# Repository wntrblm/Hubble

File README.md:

# Hubble

Hubble is Winterbloom's re-usable development board for test jigs.

## Repository layout

This repository contains the hardware design files and firmware files for Hubble.

- **firmware/** contains the firmware source code, build scripts, and third-party dependencies. The firmware is written in C using GCC ARM.
- **hardware/** contains the hardware design files for the mainboard, jackboard, panel, and programming board. These are all created using KiCAD.
- **mechanical/** contains various designs for laser-cut and 3d-printed parts used to modify the stock test jig assembly for Hubble.

## License and contributing

Hubble is open-source hardware and software, however, licensing a project like this is a little complicated. Please take a chance to review the [LICENSE](LICENSE.md) file.

We welcome contributions! Please read our [Contributing Guide](CONTRIBUTING.md) and [Code of Conduct](CODE_OF_CONDUCT.md).

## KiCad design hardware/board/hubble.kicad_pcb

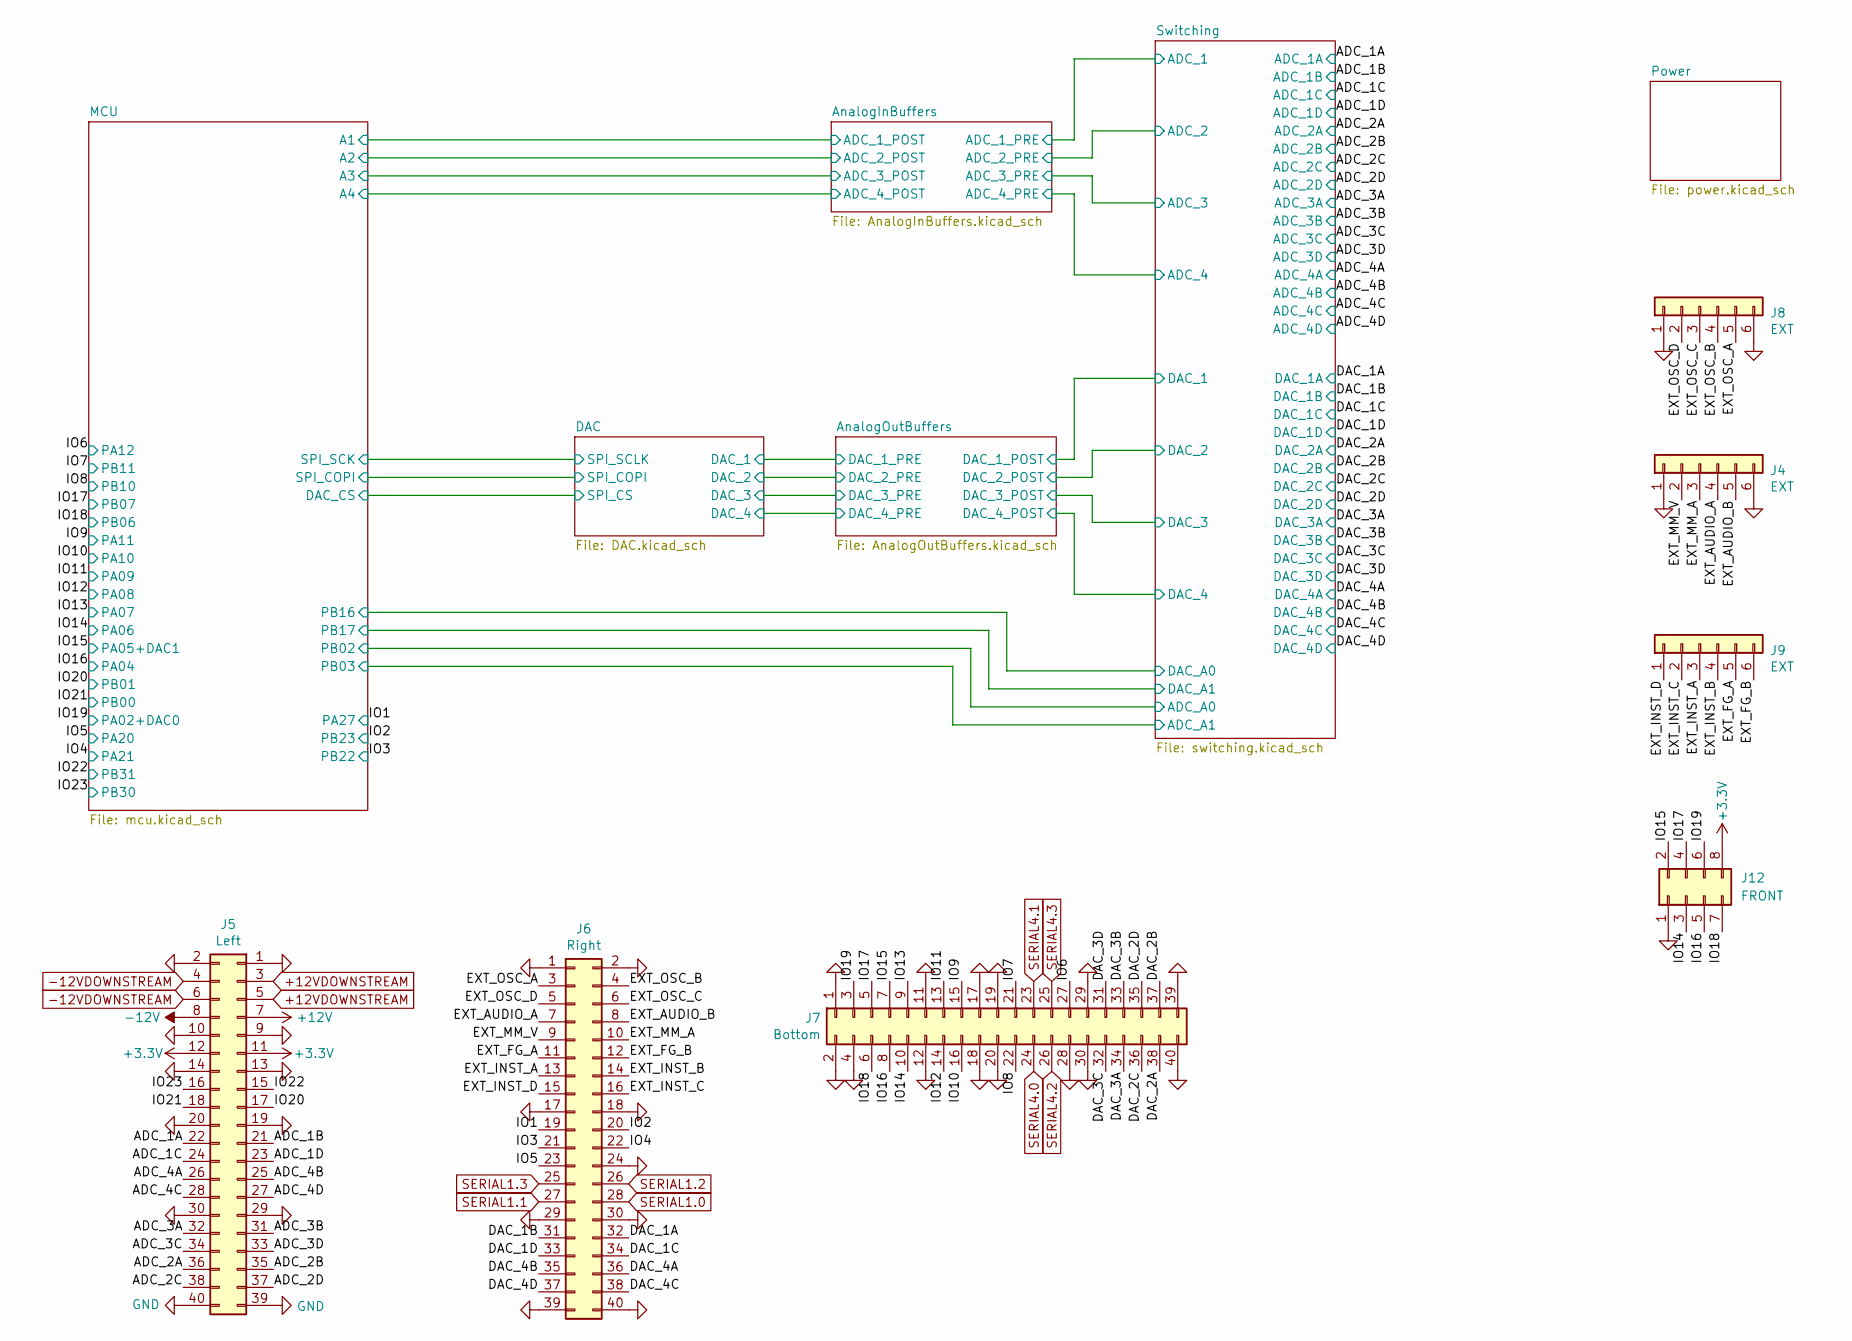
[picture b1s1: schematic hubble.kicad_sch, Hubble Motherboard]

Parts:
J4, J8, J9: EXT; SolderWire-0.75sqmm_1x06_P4.8mm_D1.25mm_OD2.3mm
J5: Left; PinSocket_2x20_P2.54mm_Vertical
J6: Right; PinSocket_2x20_P2.54mm_Vertical
J7: Bottom; PinSocket_2x20_P2.54mm_Vertical
J12: FRONT; PinHeader_2x04_P2.54mm_Vertical

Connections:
+12V: J5.7; also elsewhere on the board
+12VDOWNSTREAM: J5.3, J5.5; also elsewhere on the board
-12V: J5.8; also elsewhere on the board
-12VDOWNSTREAM: J5.4, J5.6; also elsewhere on the board
/ADC_1A: J5.22; also elsewhere on the board
/ADC_1B: J5.21; also elsewhere on the board
/ADC_1C: J5.24; also elsewhere on the board
/ADC_1D: J5.23; also elsewhere on the board
/ADC_2A: J5.36; also elsewhere on the board
/ADC_2B: J5.35; also elsewhere on the board
/ADC_2C: J5.38; also elsewhere on the board
/ADC_2D: J5.37; also elsewhere on the board
/ADC_3A: J5.32; also elsewhere on the board
/ADC_3B: J5.31; also elsewhere on the board
/ADC_3C: J5.34; also elsewhere on the board
/ADC_3D: J5.33; also elsewhere on the board
/ADC_4A: J5.26; also elsewhere on the board
/ADC_4B: J5.25; also elsewhere on the board
/ADC_4C: J5.28; also elsewhere on the board
/ADC_4D: J5.27; also elsewhere on the board
/DAC_1A: J6.32; also elsewhere on the board
/DAC_1B: J6.31; also elsewhere on the board
/DAC_1C: J6.34; also elsewhere on the board
/DAC_1D: J6.33; also elsewhere on the board
/DAC_2A: J7.38; also elsewhere on the board
/DAC_2B: J7.37; also elsewhere on the board
/DAC_2C: J7.36; also elsewhere on the board
/DAC_2D: J7.35; also elsewhere on the board
/DAC_3A: J7.34; also elsewhere on the board
/DAC_3B: J7.33; also elsewhere on the board
/DAC_3C: J7.32; also elsewhere on the board
/DAC_3D: J7.31; also elsewhere on the board
/DAC_4A: J6.36; also elsewhere on the board
/DAC_4B: J6.35; also elsewhere on the board
/DAC_4C: J6.38; also elsewhere on the board
/DAC_4D: J6.37; also elsewhere on the board
/EXT_AUDIO_A: J4.4, J6.7
/EXT_AUDIO_B: J4.5, J6.8
/EXT_FG_A: J6.11, J9.5
/EXT_FG_B: J6.12, J9.6
/EXT_INST_A: J6.13, J9.3
/EXT_INST_B: J6.14, J9.4
/EXT_INST_C: J6.16, J9.2
/EXT_INST_D: J6.15, J9.1
/EXT_MM_A: J4.3, J6.10
/EXT_MM_V: J4.2, J6.9
/EXT_OSC_A: J6.3, J8.5
/EXT_OSC_B: J6.4, J8.4
/EXT_OSC_C: J6.6, J8.3
/EXT_OSC_D: J6.5, J8.2
/IO1: J6.19; also elsewhere on the board
/IO2: J6.20; also elsewhere on the board
/IO3: J6.21; also elsewhere on the board
/IO4: J6.22; also elsewhere on the board
/IO5: J6.23; also elsewhere on the board
/IO6: J7.27; also elsewhere on the board
/IO7: J7.21; also elsewhere on the board
/IO8: J7.22; also elsewhere on the board
/IO9: J7.15; also elsewhere on the board
/IO10: J7.16; also elsewhere on the board
/IO11: J7.13; also elsewhere on the board
/IO12: J7.14; also elsewhere on the board
/IO13: J7.9; also elsewhere on the board
/IO14: J7.10, J12.3; also elsewhere on the board
/IO15: J7.7, J12.2; also elsewhere on the board
/IO16: J7.8, J12.5; also elsewhere on the board
/IO17: J7.5, J12.4; also elsewhere on the board
/IO18: J7.6, J12.7; also elsewhere on the board
/IO19: J7.3, J12.6; also elsewhere on the board
/IO20: J5.17; also elsewhere on the board
/IO21: J5.18; also elsewhere on the board
/IO22: J5.15; also elsewhere on the board
/IO23: J5.16; also elsewhere on the board
GND: J4.1, J4.6, J5.1, J5.2, J5.9, J5.10, J5.13, J5.14, J5.19, J5.20, J5.29, J5.30, J5.39, J5.40, J6.1, J6.2, J6.17, J6.18, J6.24, J6.29, J6.30, J6.39, J6.40, J7.1, J7.2, J7.4, J7.11, J7.12, J7.17, J7.18, J7.19, J7.20, J7.28, J7.29, J7.30, J7.39, J7.40, J8.1, J8.6, J12.1; also elsewhere on the board
SERIAL1.0: J6.28; also elsewhere on the board
SERIAL1.1: J6.27; also elsewhere on the board
SERIAL1.2: J6.26; also elsewhere on the board
SERIAL1.3: J6.25; also elsewhere on the board
SERIAL4.0: J7.24; also elsewhere on the board
SERIAL4.1: J7.23; also elsewhere on the board
SERIAL4.2: J7.26; also elsewhere on the board
SERIAL4.3: J7.25; also elsewhere on the board

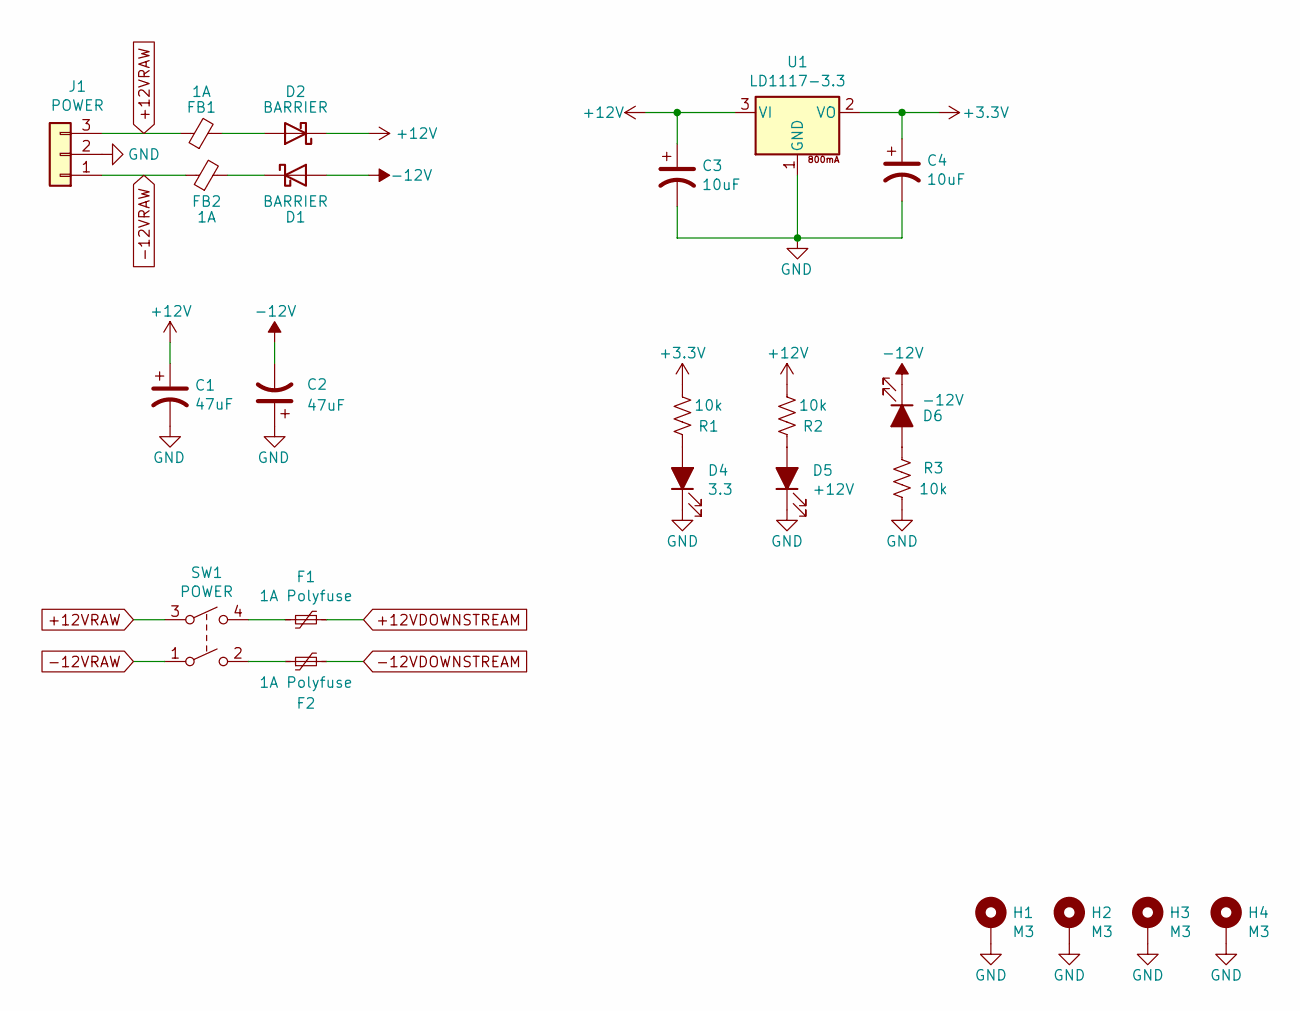
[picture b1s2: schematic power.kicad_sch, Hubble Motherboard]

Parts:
C1, C2: 47uF; CP_Radial_D5.0mm_P2.50mm
C3, C4: 10uF; CP_Radial_D5.0mm_P2.50mm
D1, D2: BARRIER; DIODE_SOD-123_SOD-123F
D4: 3.3; LED_0805_Kingbright_APT2012
D5: +12V; LED_0805_Kingbright_APT2012
D6: -12V; LED_0805_Kingbright_APT2012
F1, F2: 1A Polyfuse; Littelfuse_0805L; mpn 0805L075
FB1, FB2: 1A; L_0603_1608Metric_Pad1.05x0.95mm_HandSolder
H1, H2, H3, H4: M3; MountingHole_3.2mm_M3_Pad_Via
J1: POWER; SolderWire-0.75sqmm_1x03_P4.8mm_D1.25mm_OD2.3mm
R1, R2, R3: 10k; R_0603_1608Metric_Pad0.98x0.95mm_HandSolder
SW1: POWER; SolderWire-0.75sqmm_1x04_P4.8mm_D1.25mm_OD2.3mm
U1: LD1117-3.3; SOT-223-3_TabPin2; mpn LM1117IMP-3.3

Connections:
+12V: C1.1, C3.1, D2.1 (K), R2.1, U1.3 (VI); also elsewhere on the board
+12VDOWNSTREAM: F1.1; also elsewhere on the board
+12VRAW: FB1.1, J1.3, SW1.3
-12V: C2.2, D1.2 (A), D6.1 (K); also elsewhere on the board
-12VDOWNSTREAM: F2.2; also elsewhere on the board
-12VRAW: FB2.1, J1.1, SW1.1
GND: C1.2, C2.1, C3.2, C4.2, D4.1 (K), D5.1 (K), H1.1, H2.1, H3.1, H4.1, J1.2, R3.1, U1.1 (GND); also elsewhere on the board
unnamed: D1.1 (K), FB2.2
unnamed: D2.2 (A), FB1.2
unnamed: D4.2 (A), R1.2
unnamed: D5.2 (A), R2.2
unnamed: D6.2 (A), R3.2
unnamed: F1.2, SW1.4
unnamed: F2.1, SW1.2

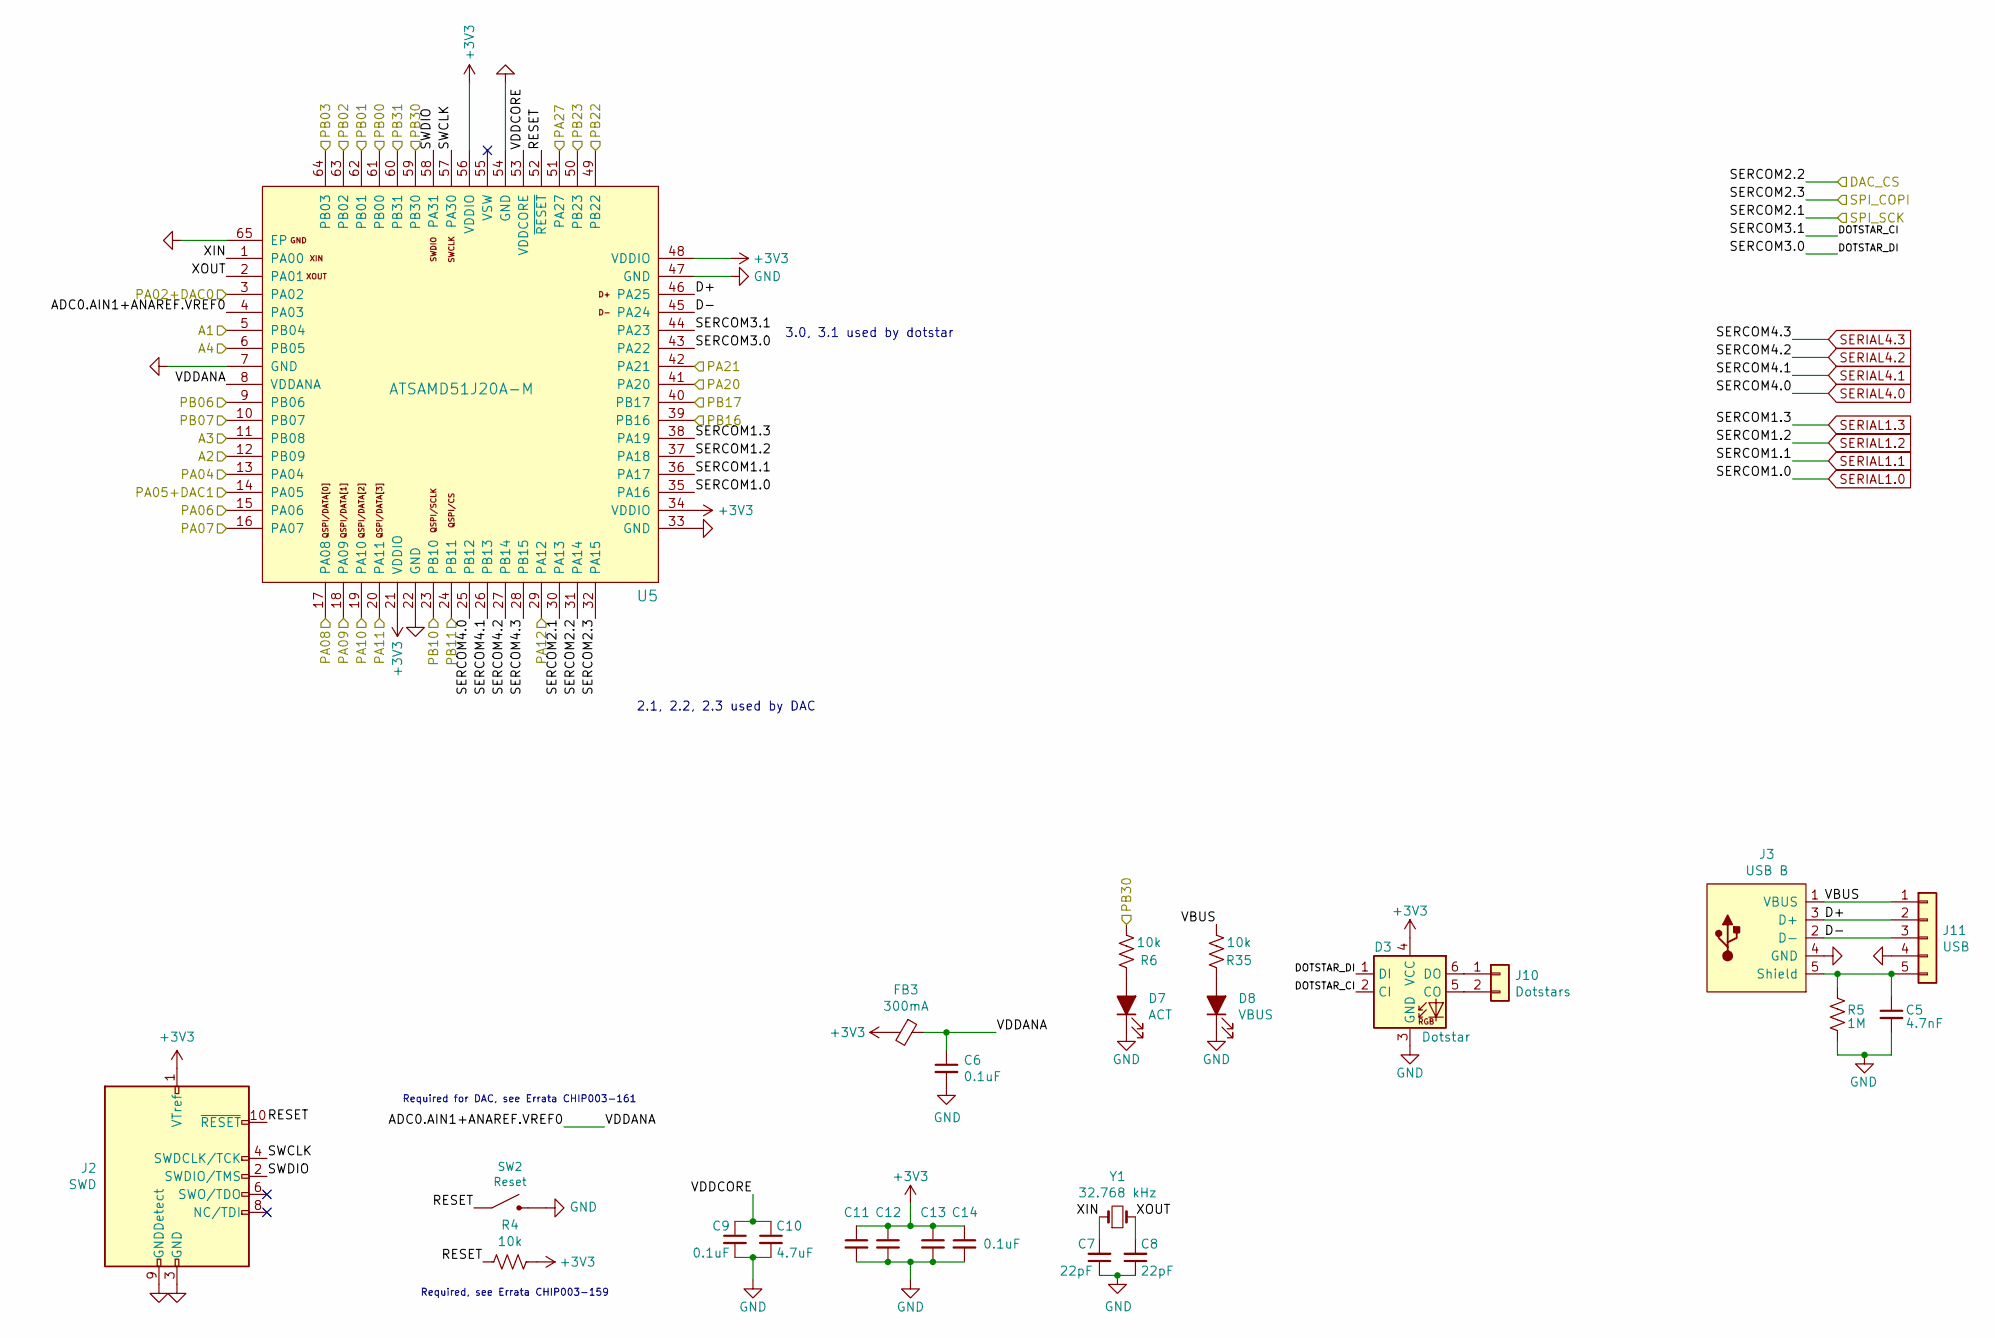
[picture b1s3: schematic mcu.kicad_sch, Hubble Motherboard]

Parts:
C5: 4.7nF; C_0603_1608Metric_Pad1.08x0.95mm_HandSolder
C6, C9, C11, C12, C13, C14: 0.1uF; C_0603_1608Metric_Pad1.08x0.95mm_HandSolder
C7, C8: 22pF; C_0603_1608Metric_Pad1.08x0.95mm_HandSolder
C10: 4.7uF; C_0603_1608Metric_Pad1.08x0.95mm_HandSolder
D3: Dotstar; Dotstar_5050; mpn SK9822
D7: ACT; LED_0805_Kingbright_APT2012
D8: VBUS; LED_0805_Kingbright_APT2012
FB3: 300mA; L_0603_1608Metric_Pad1.05x0.95mm_HandSolder
J2: SWD; PinHeader_2x05_P1.27mm_Vertical
J3: USB B; USB_B_OST_USB-B1HSxx_Horizontal; mpn 5787834-1
J10: Dotstars; PinHeader_1x02_P2.54mm_Vertical
J11: USB; PinHeader_1x05_P2.54mm_Vertical
R4, R6, R35: 10k; R_0603_1608Metric_Pad0.98x0.95mm_HandSolder
R5: 1M; R_0805_2012Metric_Pad1.20x1.40mm_HandSolder
SW2: Reset; Tactile_Switch_4.2mm; mpn MF-SW-TACT-4.2MM, MF-SW-TACT-6MM
U5: ATSAMD51J20A-M; QFN+QFP-64-SAMD51; mpn ATSAMD51J20A-M
Y1: 32.768 kHz; Crystal_SMD_2012-2Pin_2.0x1.2mm_HandSoldering

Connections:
/DAC/SPI_COPI: U5.32 (PA15); also elsewhere on the board
/IO1: U5.51 (PA27); also elsewhere on the board
/IO2: U5.50 (PB23); also elsewhere on the board
/IO3: U5.49 (PB22); also elsewhere on the board
/IO4: U5.42 (PA21); also elsewhere on the board
/IO5: U5.41 (PA20); also elsewhere on the board
/IO6: U5.29 (PA12); also elsewhere on the board
/IO7: U5.24 (PB11); also elsewhere on the board
/IO8: U5.23 (PB10); also elsewhere on the board
/IO9: U5.20 (PA11); also elsewhere on the board
/IO10: U5.19 (PA10); also elsewhere on the board
/IO11: U5.18 (PA09); also elsewhere on the board
/IO12: U5.17 (PA08); also elsewhere on the board
/IO13: U5.16 (PA07); also elsewhere on the board
/IO14: U5.15 (PA06); also elsewhere on the board
/IO15: U5.14 (PA05); also elsewhere on the board
/IO16: U5.13 (PA04); also elsewhere on the board
/IO17: U5.10 (PB07); also elsewhere on the board
/IO18: U5.9 (PB06); also elsewhere on the board
/IO19: U5.3 (PA02); also elsewhere on the board
/IO20: U5.62 (PB01); also elsewhere on the board
/IO21: U5.61 (PB00); also elsewhere on the board
/IO22: U5.60 (PB31); also elsewhere on the board
/IO23: R6.1, U5.59 (PB30); also elsewhere on the board
/MCU/ADC0.AIN1+ANAREF.VREF0: C6.1, FB3.1, U5.4 (PA03), U5.8 (VDDANA)
/MCU/D+: J3.3 (D+), J11.2, U5.46 (PA25)
/MCU/D-: J3.2 (D-), J11.3, U5.45 (PA24)
/MCU/DAC_CS: U5.31 (PA14); also elsewhere on the board
/MCU/DOTSTAR_CI: D3.2 (CI), U5.44 (PA23)
/MCU/DOTSTAR_DI: D3.1 (DI), U5.43 (PA22)
/MCU/RESET: J2.10 (~RESET), R4.1, SW2.1, U5.52 (~RESET)
/MCU/SPI_SCK: U5.30 (PA13); also elsewhere on the board
/MCU/SWCLK: J2.4 (SWDCLK/TCK), U5.57 (PA30)
/MCU/SWDIO: J2.2 (SWDIO/TMS), U5.58 (PA31)
/MCU/VBUS: J3.1 (VBUS), J11.1, R35.1
/MCU/VDDCORE: C9.1, C10.1, U5.53 (VDDCORE)
/MCU/XIN: C7.2, U5.1 (PA00), Y1.1
/MCU/XOUT: C8.2, U5.2 (PA01), Y1.2
/Switching/ADC_A0: U5.63 (PB02); also elsewhere on the board
/Switching/ADC_A1: U5.64 (PB03); also elsewhere on the board
/Switching/DAC_A0: U5.39 (PB16); also elsewhere on the board
/Switching/DAC_A1: U5.40 (PB17); also elsewhere on the board
GND: C5.2, C6.2, C7.1, C8.1, C9.2, C10.2, C11.2, C12.2, C13.2, C14.2, D3.3 (GND), D7.1 (K), D8.1 (K), J2.3 (GND), J2.5 (GND), J2.9 (GNDDetect), J3.4 (GND), J11.4, R5.2, SW2.2, U5.7 (GND), U5.22 (GND), U5.33 (GND), U5.47 (GND), U5.54 (GND), U5.65 (EP); also elsewhere on the board
unnamed: C5.1, J3.5 (Shield), J11.5, R5.1
unnamed: D3.5 (CO), J10.2
unnamed: D3.6 (DO), J10.1
unnamed: D7.2 (A), R6.2
unnamed: D8.2 (A), R35.2
SERIAL1.0: U5.35 (PA16); also elsewhere on the board
SERIAL1.1: U5.36 (PA17); also elsewhere on the board
SERIAL1.2: U5.37 (PA18); also elsewhere on the board
SERIAL1.3: U5.38 (PA19); also elsewhere on the board
SERIAL4.0: U5.25 (PB12); also elsewhere on the board
SERIAL4.1: U5.26 (PB13); also elsewhere on the board
SERIAL4.2: U5.27 (PB14); also elsewhere on the board
SERIAL4.3: U5.28 (PB15); also elsewhere on the board

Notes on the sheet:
2.1, 2.2, 2.3 used by DAC
3.0, 3.1 used by dotstar
Required, see Errata CHIP003-159
Required for DAC, see Errata CHIP003-161

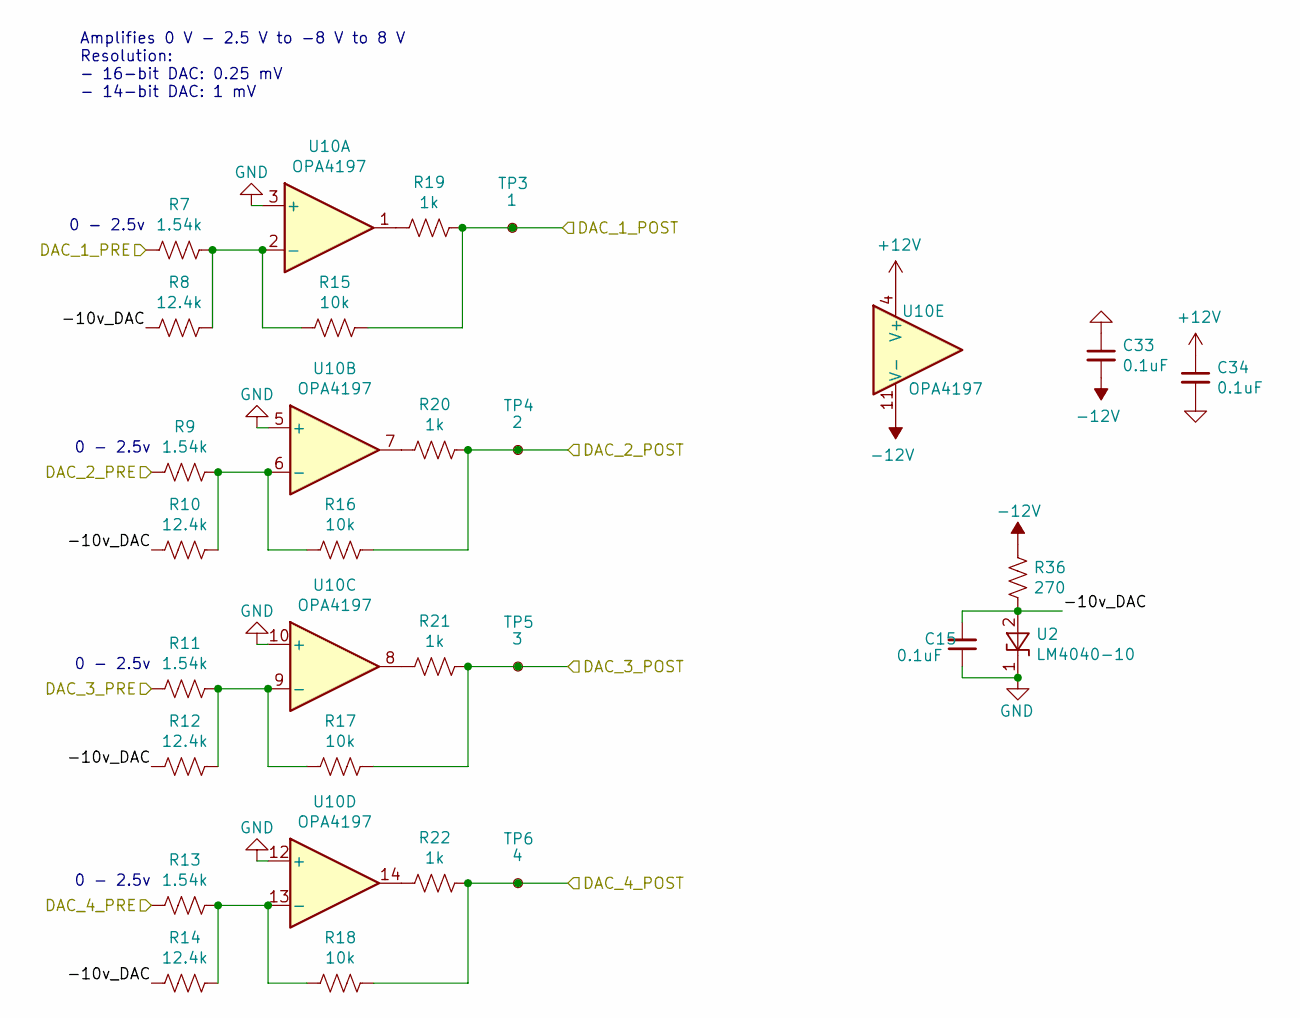
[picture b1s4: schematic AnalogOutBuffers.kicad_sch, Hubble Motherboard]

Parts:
C15, C33, C34: 0.1uF; C_0603_1608Metric_Pad1.08x0.95mm_HandSolder
R7, R9, R11, R13: 1.54k; R_0603_1608Metric_Pad0.98x0.95mm_HandSolder
R8, R10, R12, R14: 12.4k; R_0603_1608Metric_Pad0.98x0.95mm_HandSolder
R15, R16, R17, R18: 10k; R_0603_1608Metric_Pad0.98x0.95mm_HandSolder
R19, R20, R21, R22: 1k; R_0603_1608Metric_Pad0.98x0.95mm_HandSolder
R36: 270; R_0603_1608Metric_Pad0.98x0.95mm_HandSolder
TP3: 1; TestPoint_Pad_D1.0mm
TP4: 2; TestPoint_Pad_D1.0mm
TP5: 3; TestPoint_Pad_D1.0mm
TP6: 4; TestPoint_Pad_D1.0mm
U2: LM4040-10; SOT-23; mpn LM4040DIM3-10.0/NOPB
U10: OPA4197; TSSOP-14_4.4x5mm_P0.65mm; mpn OPA4197IPW

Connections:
+12V: C34.1, U10.4 (V+); also elsewhere on the board
-12V: C33.2, R36.1, U10.11 (V-); also elsewhere on the board
/AnalogOutBuffers/-10v_DAC: C15.2, R8.2, R10.2, R12.2, R14.2, R36.2, U2.2 (A)
/DAC/DAC_1: R7.2; also elsewhere on the board
/DAC/DAC_2: R9.2; also elsewhere on the board
/DAC/DAC_3: R11.2; also elsewhere on the board
/DAC/DAC_4: R13.2; also elsewhere on the board
/Switching/DAC_1: R15.1, R19.1, TP3.1; also elsewhere on the board
/Switching/DAC_2: R16.1, R20.1, TP4.1; also elsewhere on the board
/Switching/DAC_3: R17.1, R21.1, TP5.1; also elsewhere on the board
/Switching/DAC_4: R18.1, R22.1, TP6.1; also elsewhere on the board
GND: C15.1, C33.1, C34.2, U2.1 (K), U10.3 (+), U10.5 (+), U10.10 (+), U10.12 (+); also elsewhere on the board
unnamed: R9.1, R10.1, R16.2, U10.6 (-)
unnamed: R11.1, R12.1, R17.2, U10.9 (-)
unnamed: R13.1, R14.1, R18.2, U10.13 (-)
unnamed: R7.1, R8.1, R15.2, U10.2 (-)
unnamed: R19.2, U10.1
unnamed: R20.2, U10.7
unnamed: R21.2, U10.8
unnamed: R22.2, U10.14

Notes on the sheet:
0 - 2.5v
Amplifies 0 V - 2.5 V to -8 V to 8 V Resolution: - 16-bit DAC: 0.25 mV - 14-bit DAC: 1 mV

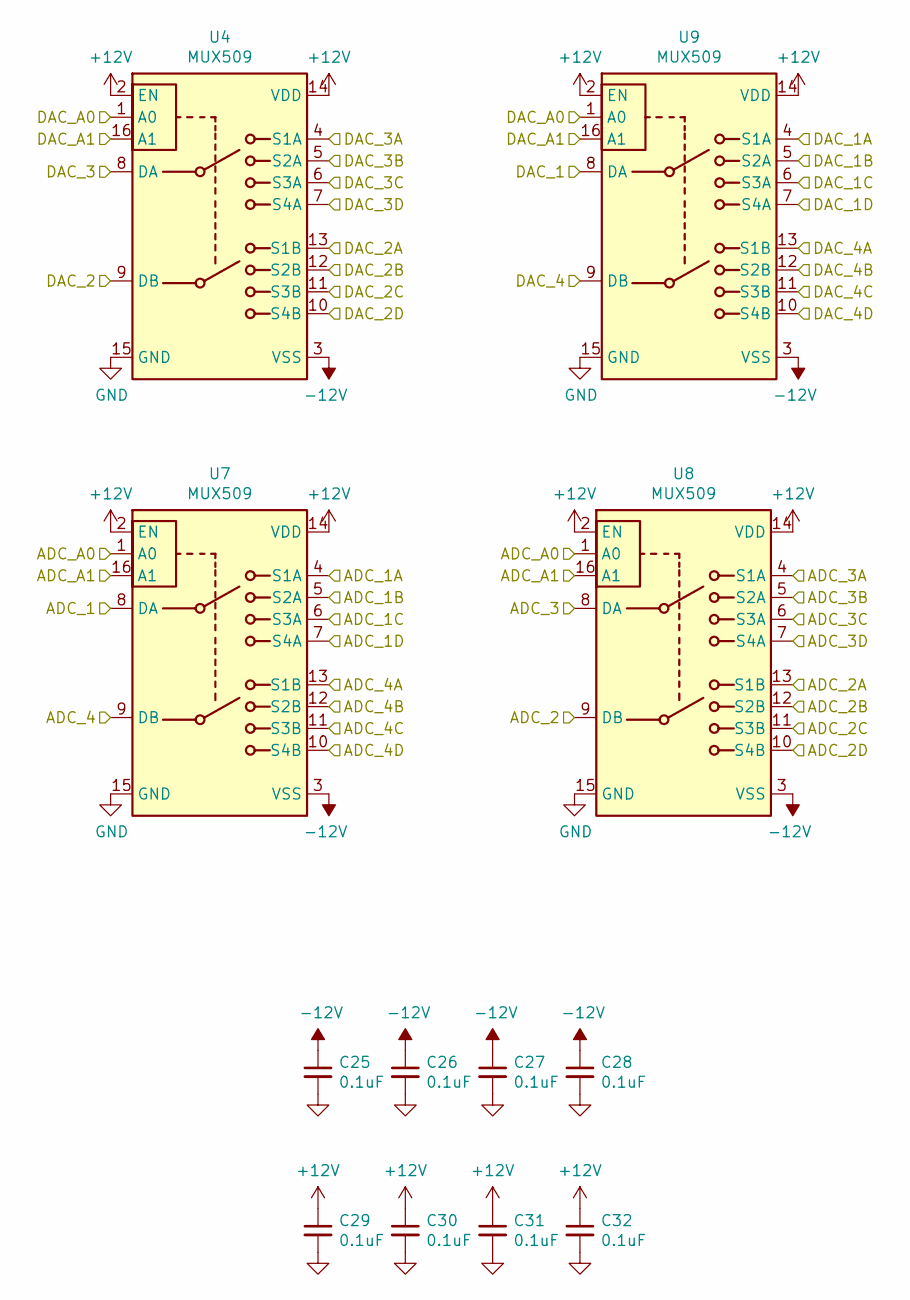
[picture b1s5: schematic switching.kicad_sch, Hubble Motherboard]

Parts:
C25, C26, C27, C28, C29, C30, C31, C32: 0.1uF; C_0603_1608Metric_Pad1.08x0.95mm_HandSolder
U4, U7, U8, U9: MUX509; TSSOP-16_4.4x5mm_P0.65mm

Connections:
+12V: C29.1, C30.1, C31.1, C32.1, U4.2 (EN), U4.14 (VDD), U7.2 (EN), U7.14 (VDD), U8.2 (EN), U8.14 (VDD), U9.2 (EN), U9.14 (VDD); also elsewhere on the board
-12V: C25.1, C26.1, C27.1, C28.1, U4.3 (VSS), U7.3 (VSS), U8.3 (VSS), U9.3 (VSS); also elsewhere on the board
/ADC_1A: U7.4 (S1A); also elsewhere on the board
/ADC_1B: U7.5 (S2A); also elsewhere on the board
/ADC_1C: U7.6 (S3A); also elsewhere on the board
/ADC_1D: U7.7 (S4A); also elsewhere on the board
/ADC_2A: U8.13 (S1B); also elsewhere on the board
/ADC_2B: U8.12 (S2B); also elsewhere on the board
/ADC_2C: U8.11 (S3B); also elsewhere on the board
/ADC_2D: U8.10 (S4B); also elsewhere on the board
/ADC_3A: U8.4 (S1A); also elsewhere on the board
/ADC_3B: U8.5 (S2A); also elsewhere on the board
/ADC_3C: U8.6 (S3A); also elsewhere on the board
/ADC_3D: U8.7 (S4A); also elsewhere on the board
/ADC_4A: U7.13 (S1B); also elsewhere on the board
/ADC_4B: U7.12 (S2B); also elsewhere on the board
/ADC_4C: U7.11 (S3B); also elsewhere on the board
/ADC_4D: U7.10 (S4B); also elsewhere on the board
/DAC_1A: U9.4 (S1A); also elsewhere on the board
/DAC_1B: U9.5 (S2A); also elsewhere on the board
/DAC_1C: U9.6 (S3A); also elsewhere on the board
/DAC_1D: U9.7 (S4A); also elsewhere on the board
/DAC_2A: U4.13 (S1B); also elsewhere on the board
/DAC_2B: U4.12 (S2B); also elsewhere on the board
/DAC_2C: U4.11 (S3B); also elsewhere on the board
/DAC_2D: U4.10 (S4B); also elsewhere on the board
/DAC_3A: U4.4 (S1A); also elsewhere on the board
/DAC_3B: U4.5 (S2A); also elsewhere on the board
/DAC_3C: U4.6 (S3A); also elsewhere on the board
/DAC_3D: U4.7 (S4A); also elsewhere on the board
/DAC_4A: U9.13 (S1B); also elsewhere on the board
/DAC_4B: U9.12 (S2B); also elsewhere on the board
/DAC_4C: U9.11 (S3B); also elsewhere on the board
/DAC_4D: U9.10 (S4B); also elsewhere on the board
/Switching/ADC_1: U7.8 (DA); also elsewhere on the board
/Switching/ADC_2: U8.9 (DB); also elsewhere on the board
/Switching/ADC_3: U8.8 (DA); also elsewhere on the board
/Switching/ADC_4: U7.9 (DB); also elsewhere on the board
/Switching/ADC_A0: U7.1 (A0), U8.1 (A0); also elsewhere on the board
/Switching/ADC_A1: U7.16 (A1), U8.16 (A1); also elsewhere on the board
/Switching/DAC_1: U9.8 (DA); also elsewhere on the board
/Switching/DAC_2: U4.9 (DB); also elsewhere on the board
/Switching/DAC_3: U4.8 (DA); also elsewhere on the board
/Switching/DAC_4: U9.9 (DB); also elsewhere on the board
/Switching/DAC_A0: U4.1 (A0), U9.1 (A0); also elsewhere on the board
/Switching/DAC_A1: U4.16 (A1), U9.16 (A1); also elsewhere on the board
GND: C25.2, C26.2, C27.2, C28.2, C29.2, C30.2, C31.2, C32.2, U4.15 (GND), U7.15 (GND), U8.15 (GND), U9.15 (GND); also elsewhere on the board

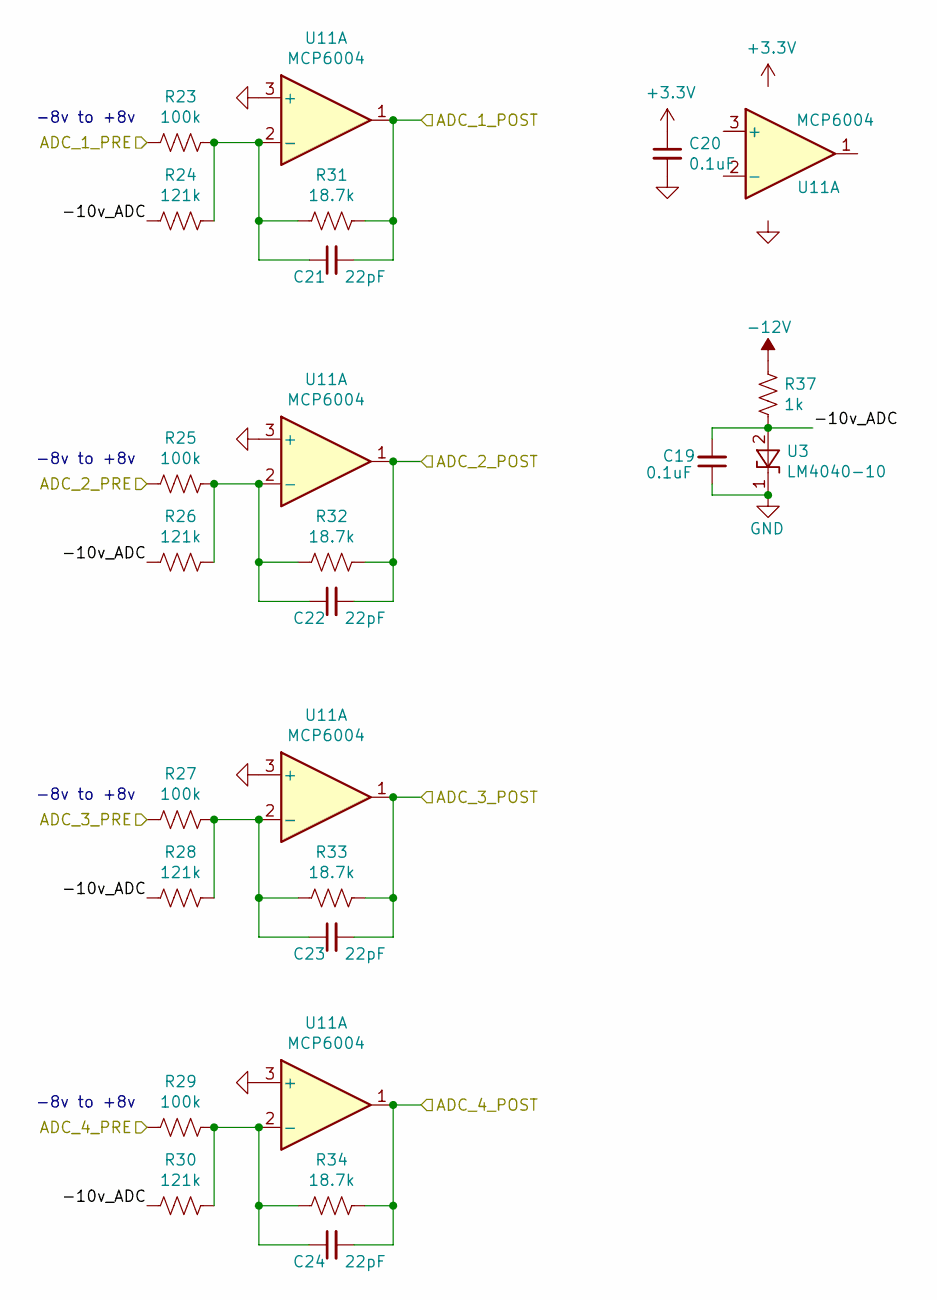
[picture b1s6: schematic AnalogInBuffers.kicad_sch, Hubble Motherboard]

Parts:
C19, C20: 0.1uF; C_0603_1608Metric_Pad1.08x0.95mm_HandSolder
C21, C22, C23, C24: 22pF; C_0603_1608Metric_Pad1.08x0.95mm_HandSolder
R23, R25, R27, R29: 100k; R_0603_1608Metric_Pad0.98x0.95mm_HandSolder
R24, R26, R28, R30: 121k; R_0603_1608Metric_Pad0.98x0.95mm_HandSolder
R31, R32, R33, R34: 18.7k; R_0603_1608Metric_Pad0.98x0.95mm_HandSolder
R37: 1k; R_0603_1608Metric_Pad0.98x0.95mm_HandSolder
U3: LM4040-10; SOT-23; mpn LM4040DIM3-10.0/NOPB
U11: MCP6004; TSSOP-14_4.4x5mm_P0.65mm; mpn MCP6004T-I/ST, MCP6004T-E/ST

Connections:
-12V: R37.1; also elsewhere on the board
/AnalogInBuffers/-10v_ADC: C19.2, R24.2, R26.2, R28.2, R30.2, R37.2, U3.2 (A)
/Switching/ADC_1: R23.2; also elsewhere on the board
/Switching/ADC_2: R25.2; also elsewhere on the board
/Switching/ADC_3: R27.2; also elsewhere on the board
/Switching/ADC_4: R29.2; also elsewhere on the board
GND: C19.1, C20.2, U3.1 (K), U11.3 (+), U11.5 (+), U11.10 (+), U11.11 (V-), U11.12 (+); also elsewhere on the board

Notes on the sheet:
-8v to +8v

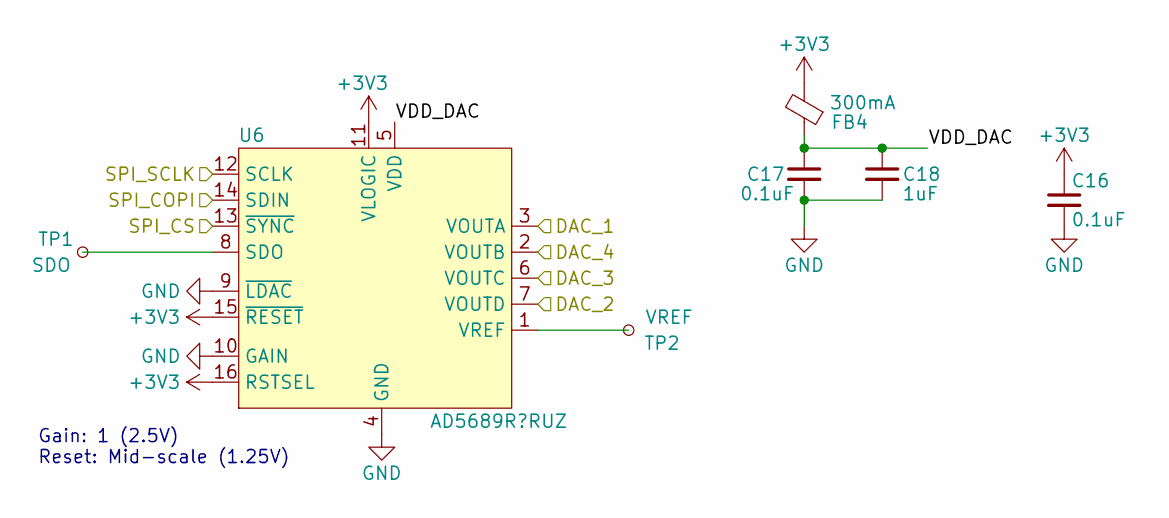
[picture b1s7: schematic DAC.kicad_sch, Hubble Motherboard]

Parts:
C16, C17: 0.1uF; C_0603_1608Metric_Pad1.08x0.95mm_HandSolder
C18: 1uF; C_0603_1608Metric_Pad1.08x0.95mm_HandSolder
FB4: 300mA; L_0603_1608Metric_Pad1.05x0.95mm_HandSolder
TP1: SDO; TestPoint_Pad_D1.0mm
TP2: VREF; TestPoint_Pad_D1.0mm
U6: AD5689R?RUZ; TSSOP-16_4.4x5mm_P0.65mm; mpn AD5685ARUZ, AD5685BRUZ

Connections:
/DAC/DAC_1: U6.3 (VOUTA); also elsewhere on the board
/DAC/DAC_2: U6.7 (VOUTD); also elsewhere on the board
/DAC/DAC_3: U6.6 (VOUTC); also elsewhere on the board
/DAC/DAC_4: U6.2 (VOUTB); also elsewhere on the board
/DAC/SPI_COPI: U6.14 (SDIN); also elsewhere on the board
/DAC/VDD_DAC: C17.1, C18.1, FB4.1, U6.5 (VDD)
/MCU/DAC_CS: U6.13 (~SYNC); also elsewhere on the board
/MCU/SPI_SCK: U6.12 (SCLK); also elsewhere on the board
GND: C16.2, C17.2, C18.2, U6.4 (GND), U6.9 (~LDAC), U6.10 (GAIN); also elsewhere on the board
unnamed: TP1.1, U6.8 (SDO)
unnamed: TP2.1, U6.1 (VREF)

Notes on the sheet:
Gain: 1 (2.5V) Reset: Mid-scale (1.25V)

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
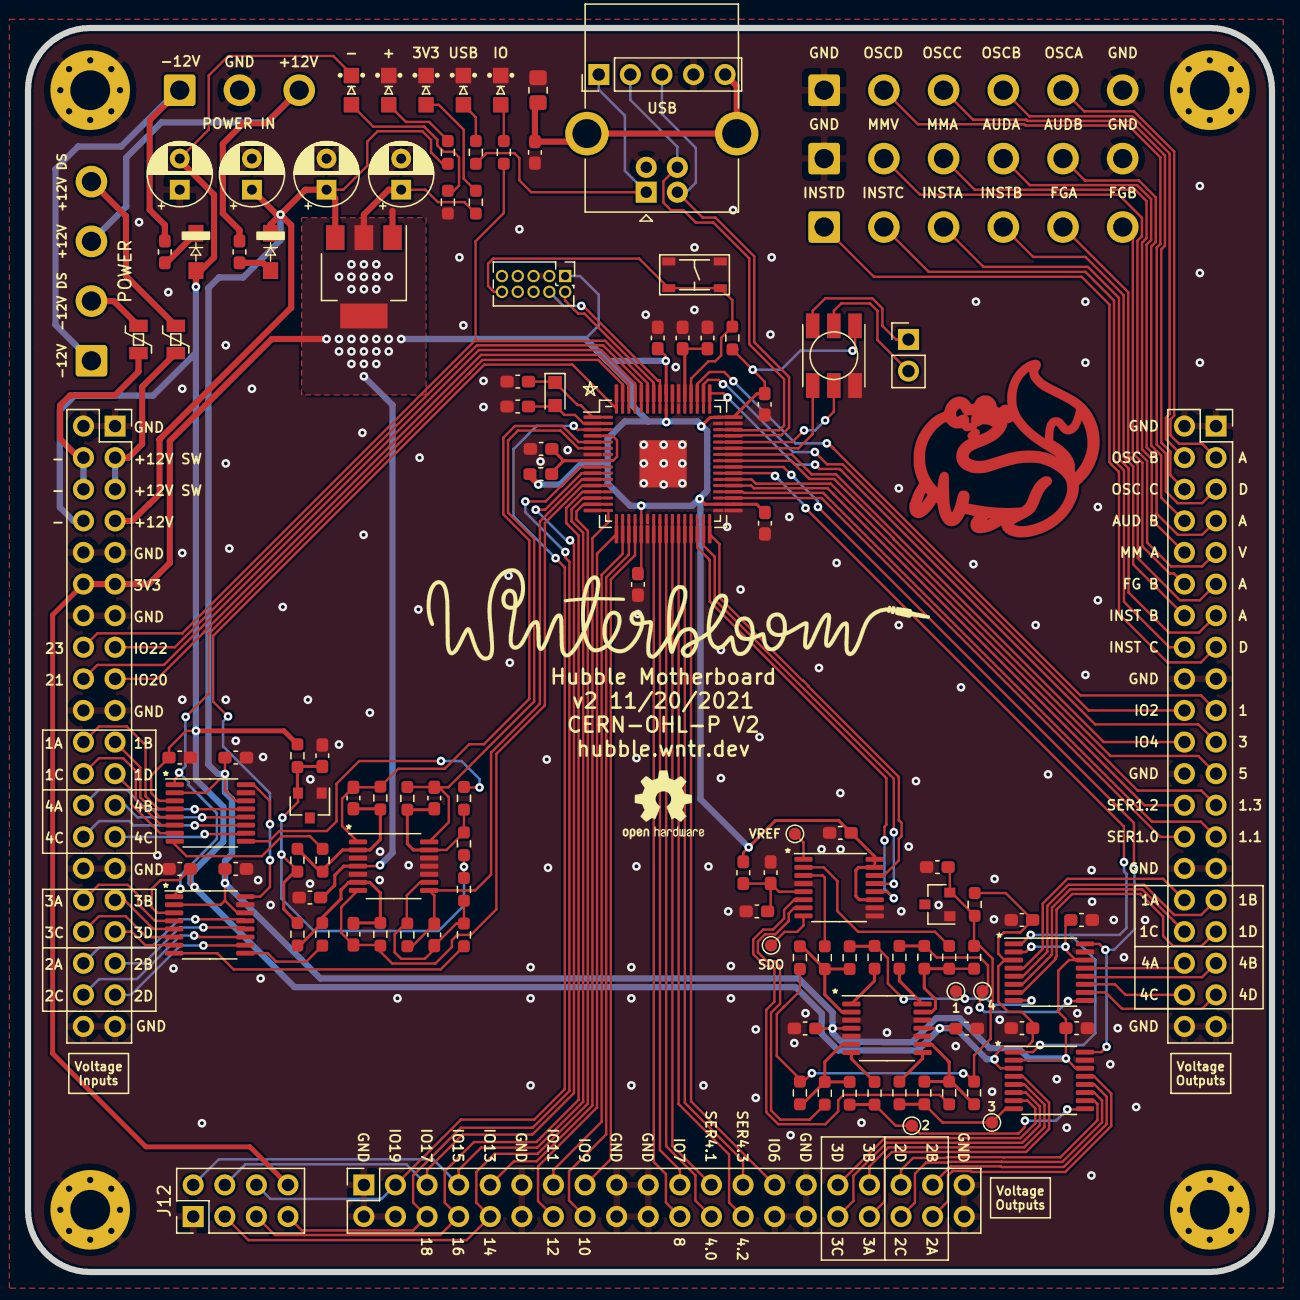
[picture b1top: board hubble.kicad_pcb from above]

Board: 2 copper layers, 100.0 x 100.0 mm, 121 parts (0 on the bottom side), 149 nets.

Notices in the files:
hardware/16_bit_analog_out/16_bit_analog_out.kicad_pcb:
CERN OHL-P V2
